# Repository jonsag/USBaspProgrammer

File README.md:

# USBaspProgrammer

My adaption of [Thomas Fischl's construction](https://www.fischl.de/usbasp/).  

This README concentrates on using ATmega88, and uploading it with avrisp, with a device such as [this one](https://github.com/jonsag/ardAVRProgrammer).  
Use the ICSP header on the programmer, and remember to set jumper J2.  

## Compile and upload

Put the ATmega88 in the programming device, and  

>$ cd Firmware/firmware

Test avrdude  

>$ make avrdude

    avrdude -c avrisp -p atmega88 -P /dev/ttyUSB0 -b 19200 -v

    avrdude: Version 6.3
            Copyright (c) 2000-2005 Brian Dean, http://www.bdmicro.com/
            Copyright (c) 2007-2014 Joerg Wunsch

            System wide configuration file is "/etc/avrdude.conf"
            User configuration file is "/home/jon/.avrduderc"
            User configuration file does not exist or is not a regular file, skipping

            Using Port                    : /dev/ttyUSB0
            Using Programmer              : avrisp
            Overriding Baud Rate          : 19200
            AVR Part                      : ATmega88
            Chip Erase delay              : 9000 us
            PAGEL                         : PD7
            BS2                           : PC2
            RESET disposition             : dedicated
            RETRY pulse                   : SCK
            serial program mode           : yes
            parallel program mode         : yes
            Timeout                       : 200
            StabDelay                     : 100
            CmdexeDelay                   : 25
            SyncLoops                     : 32
            ByteDelay                     : 0
            PollIndex                     : 3
            PollValue                     : 0x53
            Memory Detail                 :

                                    Block Poll               Page                       Polled
            Memory Type Mode Delay Size  Indx Paged  Size   Size #Pages MinW  MaxW   ReadBack
            ----------- ---- ----- ----- ---- ------ ------ ---- ------ ----- ----- ---------
            eeprom        65    20     4    0 no        512    4      0  3600  3600 0xff 0xff
            flash         65     6    64    0 yes      8192   64    128  4500  4500 0xff 0xff
            lfuse          0     0     0    0 no          1    0      0  4500  4500 0x00 0x00
            hfuse          0     0     0    0 no          1    0      0  4500  4500 0x00 0x00
            efuse          0     0     0    0 no          1    0      0  4500  4500 0x00 0x00
            lock           0     0     0    0 no          1    0      0  4500  4500 0x00 0x00
            calibration    0     0     0    0 no          1    0      0     0     0 0x00 0x00
            signature      0     0     0    0 no          3    0      0     0     0 0x00 0x00

            Programmer Type : STK500
            Description     : Atmel AVR ISP
            Hardware Version: 2
            Firmware Version: 1.18
            Topcard         : Unknown
            Vtarget         : 0.0 V
            Varef           : 0.0 V
            Oscillator      : Off
            SCK period      : 0.1 us

    avrdude: AVR device initialized and ready to accept instructions

    Reading | ################################################## | 100% 0.08s

    avrdude: Device signature = 0x1e930a (probably m88)
    avrdude: safemode: hfuse reads as DF
    avrdude: safemode: efuse reads as F9

    avrdude: safemode: hfuse reads as DF
    avrdude: safemode: efuse reads as F9
    avrdude: safemode: Fuses OK (E:F9, H:DF, L:62)

    avrdude done.  Thank you.

Clean, compile, upload and set fuses  

>$ make clean

    rm -f main.hex main.lst main.obj main.cof main.list main.map main.eep.hex main.bin *.o main.s usbdrv/*.o

>$ make main.hex

    avr-gcc -Wall -O2 -Iusbdrv -I. -mmcu=atmega88  -c usbdrv/usbdrv.c -o usbdrv/usbdrv.o
    avr-gcc -Wall -O2 -Iusbdrv -I. -mmcu=atmega88  -x assembler-with-cpp -c usbdrv/usbdrvasm.S -o usbdrv/usbdrvasm.o
    avr-gcc -Wall -O2 -Iusbdrv -I. -mmcu=atmega88  -c usbdrv/oddebug.c -o usbdrv/oddebug.o
    avr-gcc -Wall -O2 -Iusbdrv -I. -mmcu=atmega88  -c isp.c -o isp.o
    avr-gcc -Wall -O2 -Iusbdrv -I. -mmcu=atmega88  -c clock.c -o clock.o
    avr-gcc -Wall -O2 -Iusbdrv -I. -mmcu=atmega88  -x assembler-with-cpp -c tpi.S -o tpi.o
    avr-gcc -Wall -O2 -Iusbdrv -I. -mmcu=atmega88  -c main.c -o main.o
    avr-gcc -Wall -O2 -Iusbdrv -I. -mmcu=atmega88  -o main.bin usbdrv/usbdrv.o usbdrv/usbdrvasm.o usbdrv/oddebug.o isp.o clock.o tpi.o main.o -Wl,-Map,main.map
    rm -f main.hex main.eep.hex
    avr-objcopy -j .text -j .data -O ihex main.bin main.hex

>$ make flash

    avrdude -c avrisp -p atmega88 -P /dev/ttyUSB0 -b 19200 -U flash:w:main.hex

    avrdude: AVR device initialized and ready to accept instructions

    Reading | ################################################## | 100% 0.08s

    avrdude: Device signature = 0x1e930a (probably m88)
    avrdude: NOTE: "flash" memory has been specified, an erase cycle will be performed
            To disable this feature, specify the -D option.
    avrdude: erasing chip
    avrdude: reading input file "main.hex"
    avrdude: input file main.hex auto detected as Intel Hex
    avrdude: writing flash (4400 bytes):

    Writing | ################################################## | 100% 7.60s

    avrdude: 4400 bytes of flash written
    avrdude: verifying flash memory against main.hex:
    avrdude: load data flash data from input file main.hex:
    avrdude: input file main.hex auto detected as Intel Hex
    avrdude: input file main.hex contains 4400 bytes
    avrdude: reading on-chip flash data:

    Reading | ################################################## | 100% 5.38s

    avrdude: verifying ...
    avrdude: 4400 bytes of flash verified

    avrdude: safemode: Fuses OK (E:F9, H:DF, L:62)

    avrdude done.  Thank you.

>$ make fuses

    avrdude -c avrisp -p atmega88 -P /dev/ttyUSB0 -b 19200 -u -U hfuse:w:0xDD:m -U lfuse:w:0xFF:m

    avrdude: AVR device initialized and ready to accept instructions

    Reading | ################################################## | 100% 0.08s

    avrdude: Device signature = 0x1e930a (probably m88)
    avrdude: reading input file "0xDD"
    avrdude: writing hfuse (1 bytes):

    Writing | ################################################## | 100% 0.09s

    avrdude: 1 bytes of hfuse written
    avrdude: verifying hfuse memory against 0xDD:
    avrdude: load data hfuse data from input file 0xDD:
    avrdude: input file 0xDD contains 1 bytes
    avrdude: reading on-chip hfuse data:

    Reading | ################################################## | 100% 0.03s

    avrdude: verifying ...
    avrdude: 1 bytes of hfuse verified
    avrdude: reading input file "0xFF"
    avrdude: writing lfuse (1 bytes):

    Writing | ################################################## | 100% 0.09s

    avrdude: 1 bytes of lfuse written
    avrdude: verifying lfuse memory against 0xFF:
    avrdude: load data lfuse data from input file 0xFF:
    avrdude: input file 0xFF contains 1 bytes
    avrdude: reading on-chip lfuse data:

    Reading | ################################################## | 100% 0.03s

    avrdude: verifying ...
    avrdude: 1 bytes of lfuse verified

    avrdude done.  Thank you.

## Define device rules

>$ sudo cp \<PATH>/Documents/linux-nonroot/99-USBasp.rules /etc/udev/rules.d/99-USBasp.rules
>
>$ sudo udevadm control --reload-rules

## From Thomas Fischl's README

### USE PRECOMPILED VERSION  

Firmware:  
Flash "Firmware/precompiled/usbasp.atmega88.xxxx-xx-xx.hex" or "Firmware/precompiled/usbaspatmega8.xxxx-xx-xx.hex" to the used controller with a working programmer (e.g. with avrdude, uisp, ...). Set jumper J2 to activate USBasp firmware update function.  
You have to change the fuse bits for external crystal (see "make fuses").  
\# TARGET=atmega8    HFUSE=0xc9  LFUSE=0xef  
\# TARGET=atmega48   HFUSE=0xdd  LFUSE=0xff  
\# TARGET=atmega88   HFUSE=0xdd  LFUSE=0xff  

### Setting jumpers

J1 Power target  
    Supply target with 5V (USB voltage). Be careful with this option, the circuit isn't protected against short circuit!  
J2 Jumper for firmware upgrade (not self-upgradable)  
    Set this jumper for flashing the ATMega(4)8 of USBasp with another working programmer.  
J3 SCK option  
    If the target clock is lower than 1,5 MHz, you have to set this jumper. Then SCK is scaled down from 375 kHz to about 8 kHz  

### BUILDING AND INSTALLING FROM SOURCE CODE

#### Firmware

To compile the firmware  

1. install the GNU toolchain for AVR microcontrollers (avr-gcc, avr-libc),  
2. change directory to Firmware/firmware/  
3. run "make main.hex"  
4. flash "main.hex" to the ATMega(4)8. E.g. with uisp or avrdude (check the Makefile option "make flash"). To flash the firmware you have to set jumper J2 and connect USBasp to a working programmer.  
 You have to change the fuse bits for external crystal, (check the Makefile option "make fuses").  

#### Software (avrdude)

AVRDUDE supports USBasp since version 5.2.  

1. install libusb: [http://libusb.sourceforge.net/](http://libusb.sourceforge.net/)  
2. get latest avrdude release: [http://download.savannah.gnu.org/releases/avrdude/](http://download.savannah.gnu.org/releases/avrdude/)  
3. cd avrdude-X.X.X  
4. configure to your environment:  
./bootstrap (I had to comment out the two if-blocks which verify the installed versions of autoconf and automake)  
./configure  
5. compile and install it:  
make  
make install  

### Notes

To use USBasp as non-root, you have to define some device rules. See Documents/linux-nonroot for an example.  

### MORE INFORMATION

For more information on USBasp and it's components please visit the following URLs:  

USBasp .......................... [http://www.fischl.de/usbasp/](http://www.fischl.de/usbasp/)  
  
Firmware-only V-USB driver ...... [http://www.obdev.at/products/vusb/](http://www.obdev.at/products/vusb/)  
avrdude ......................... [http://www.nongnu.org/avrdude/](http://www.nongnu.org/avrdude/)  
libusb .......................... [http://libusb.sourceforge.net/](http://libusb.sourceforge.net/)  
libusb-win32 .................... [http://libusb-win32.sourceforge.net/](http://libusb-win32.sourceforge.net/)  

## Troubleshooting

### Compiling problem

    usbdrv/usbdrv.h:455:6: error: variable ‘usbDescriptorDevice’ must be const in order to be put into read-only section by means of ‘__attribute__((progmem))’
 char usbDescriptorDevice[];

Solution at [https://openrcforums.com/forum/viewtopic.php?t=2731](https://openrcforums.com/forum/viewtopic.php?t=2731), from Mon Feb 04, 2013  

    This issue is resolved I just wanted to document it here.

    Usbasp uses V-usb for usb communications. Usbasp includes V-usb in it's source code. The version of V-usb included in Usbasp is not the latest and would not compile with a recent avr-gcc. This issue affected er9x over a year ago.

    When trying to compile the 2009 or 2011 versions of Usbasp from http://www.fischl.de/usbasp/ I got about a dozen of these errors.
    CODE: SELECT ALL

    usbdrv/usbdrv.h:451:6: error: variable ‘usbDescriptorDevice’ must be const in order to be put into read-only section by means of ‘__attribute__((progmem))’
    The solution was to remove the ./firmware/usbdrv directory from the Usbasp source and replace it with the source from http://www.obdev.at/downloads/vusb/vusb-20121206.tar.gz . Then I was able to compile Usbasp. I tested both the 2009 and 2011 versions on a programmer and was able to program a MCU.

    Not sure when avr-gcc became picky about this issue or if that is even the issue. Nor do I know why my Ubuntuish 'Linux Mint 14 Nadia' calls the package gcc-avr. Anyway this is what versions of the relevant ( I think) packages I have installed.

    ii avr-libc 1:1.8.0-2 all Standard C library for Atmel AVR developm
    ii binutils-avr 2.20.1-3 amd64 Binary utilities supporting Atmel's AVR t
    ii gcc-avr 1:4.7.0-2 amd64 The GNU C compiler (cross compiler for av

## My notes

Connections on different MCUs  

            10Pin           6pin    ATmega8/88/328/328P     ATtiny4313      ATtiny85  
MOSI    ->  1           ->  4   ->  17/PB3                  17/PB5          5/AREF/PB0  
MISO    ->  9           ->  1   ->  18/PB4                  18/PB6          6/PB1  
SCK     ->  7           ->  3   ->  19/PB5                  19/PB7          7/PB2  
RST     ->  5           ->  5   ->  1/RESET/PC6,21/AREF     1/RESET/PA2     1/RESET/PB5  
VCC     ->  2           ->  2   ->  7/VCC                   20/VCC          8/VCC  
GND     ->  4,6,8,10    ->  6   ->  8/GND                   10/GND          4/GND  
XTAL1                               9/XTAL1                 5/XTAL1         2/XTAL1
XTAL2                               10/XTAL2                4/XTAL2         3/XTAL2

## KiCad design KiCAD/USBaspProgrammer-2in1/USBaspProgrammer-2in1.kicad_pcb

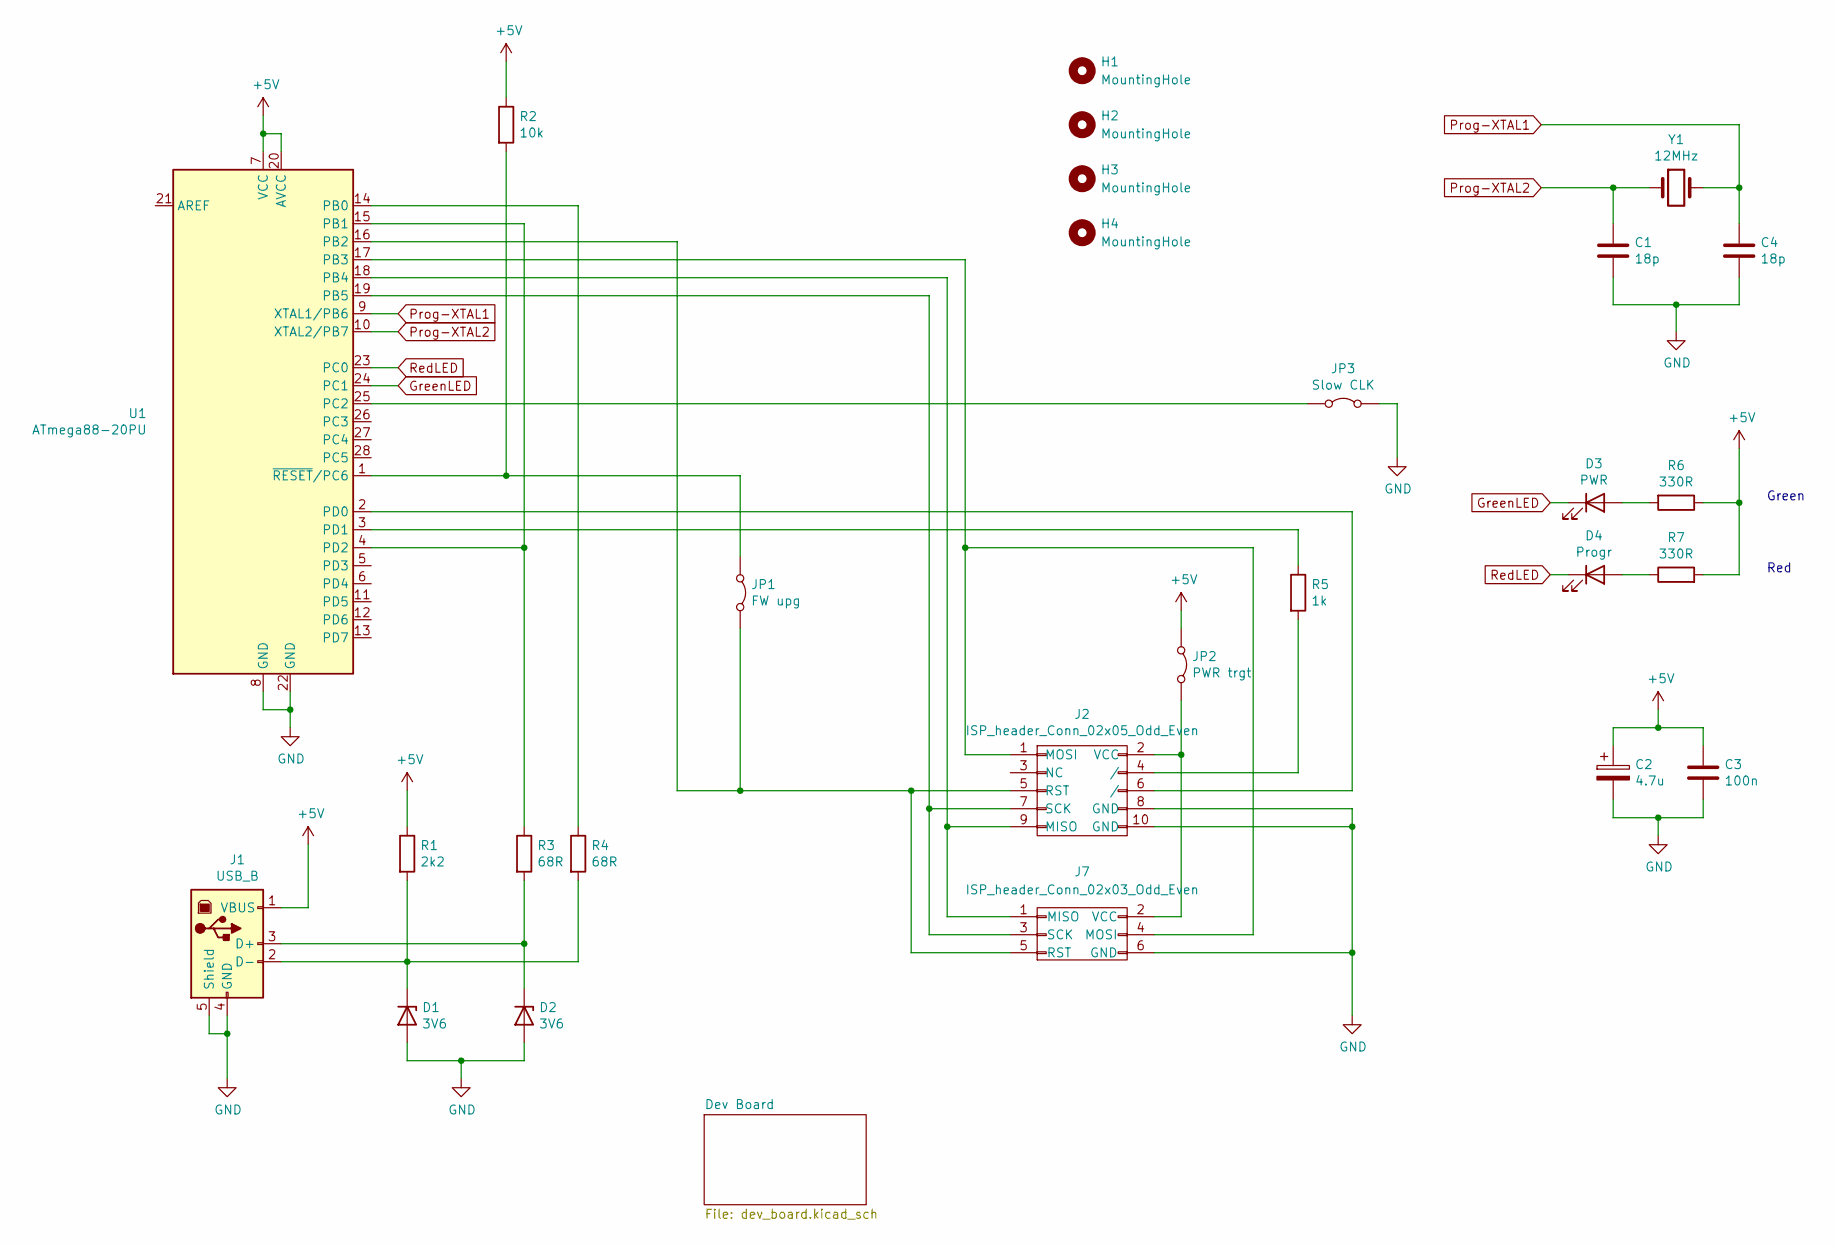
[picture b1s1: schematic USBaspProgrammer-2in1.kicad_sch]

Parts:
C1, C4: 18p; C_Disc_D3.0mm_W1.6mm_P2.50mm_larg
C2: 4.7u; CP_Radial_D5.0mm_P2.00mm_larger
C3: 100n; C_Disc_D7.5mm_W2.5mm_P5.00mm_larger
D1, D2: 3V6; D_DO-35_SOD27_P7.62mm_Horizontal_large
D3: PWR; LED_D5.0mm_larger_pads
D4: Progr; LED_D5.0mm_larger_pads
H1, H2, H3, H4: MountingHole; MountingHole_3.2mm_M3
J1: USB_B; USB_B_OST_USB-B1HSxx_Horizontal_large
J2: ISP_header_Conn_02x05_Odd_Even; IDC-Header_2x05_P2.54mm_Vertical_large
J7: ISP_header_Conn_02x03_Odd_Even; IDC-Header_2x03_P2.54mm_Horizontal_large
JP1: FW upg; Jumper_1x02_P2.54mm_large
JP2: PWR trgt; Jumper_1x02_P2.54mm_large
JP3: Slow CLK; Jumper_1x02_P2.54mm_large
R1: 2k2; R_Axial_DIN0207_L6.3mm_D2.5mm_P10.16mm_Horizontal_large
R2: 10k; R_Axial_DIN0207_L6.3mm_D2.5mm_P10.16mm_Horizontal_large
R3, R4: 68R; R_Axial_DIN0207_L6.3mm_D2.5mm_P10.16mm_Horizontal_large
R5: 1k; R_Axial_DIN0207_L6.3mm_D2.5mm_P10.16mm_Horizontal_large
R6, R7: 330R; R_Axial_DIN0207_L6.3mm_D2.5mm_P10.16mm_Horizontal_large
U1: ATmega88-20PU; DIP-28_W7.62mm_LongPads w socket
Y1: 12MHz; Crystal_HC49-4H_Vertical_large

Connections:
+5V: C2.1, C3.1, J1.1 (VBUS), JP2.1 (A), R1.1, R2.1, R6.1, R7.2, U1.7 (VCC), U1.20 (AVCC)
GND: C1.2, C2.2, C3.2, C4.2, D1.2 (A), D2.2 (A), J1.4 (GND), J1.5 (Shield), J2.8 (GND), J2.10 (GND), J7.6 (GND), JP3.2 (B), U1.8 (GND), U1.22 (GND); also elsewhere on the board
GreenLED: D3.1 (K), U1.24 (PC1)
unnamed: D1.1 (K), J1.2 (D-), R1.2, R4.2
unnamed: D2.1 (K), J1.3 (D+), R3.2
unnamed: D3.2 (A), R6.2
unnamed: D4.2 (A), R7.1
unnamed: J2.9 (MISO), J7.1 (MISO), U1.18 (PB4)
unnamed: J2.1 (MOSI), J7.4 (MOSI), U1.17 (PB3)
unnamed: J2.5 (RST), J7.5 (RST), JP1.2 (B), U1.16 (PB2)
unnamed: J2.7 (SCK), J7.3 (SCK), U1.19 (PB5)
unnamed: J2.2 (VCC), J7.2 (VCC), JP2.2 (B)
unnamed: J2.4 (/), R5.2
unnamed: JP1.1 (A), R2.2, U1.1 (~RESET/PC6)
unnamed: JP3.1 (A), U1.25 (PC2)
unnamed: R4.1, U1.14 (PB0)
unnamed: R3.1, U1.4 (PD2), U1.15 (PB1)
unnamed: J2.6 (/), U1.2 (PD0)
unnamed: R5.1, U1.3 (PD1)
Prog-XTAL1: C4.1, U1.9 (XTAL1/PB6), Y1.2
Prog-XTAL2: C1.1, U1.10 (XTAL2/PB7), Y1.1
RedLED: D4.1 (K), U1.23 (PC0)

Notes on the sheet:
Green
Red

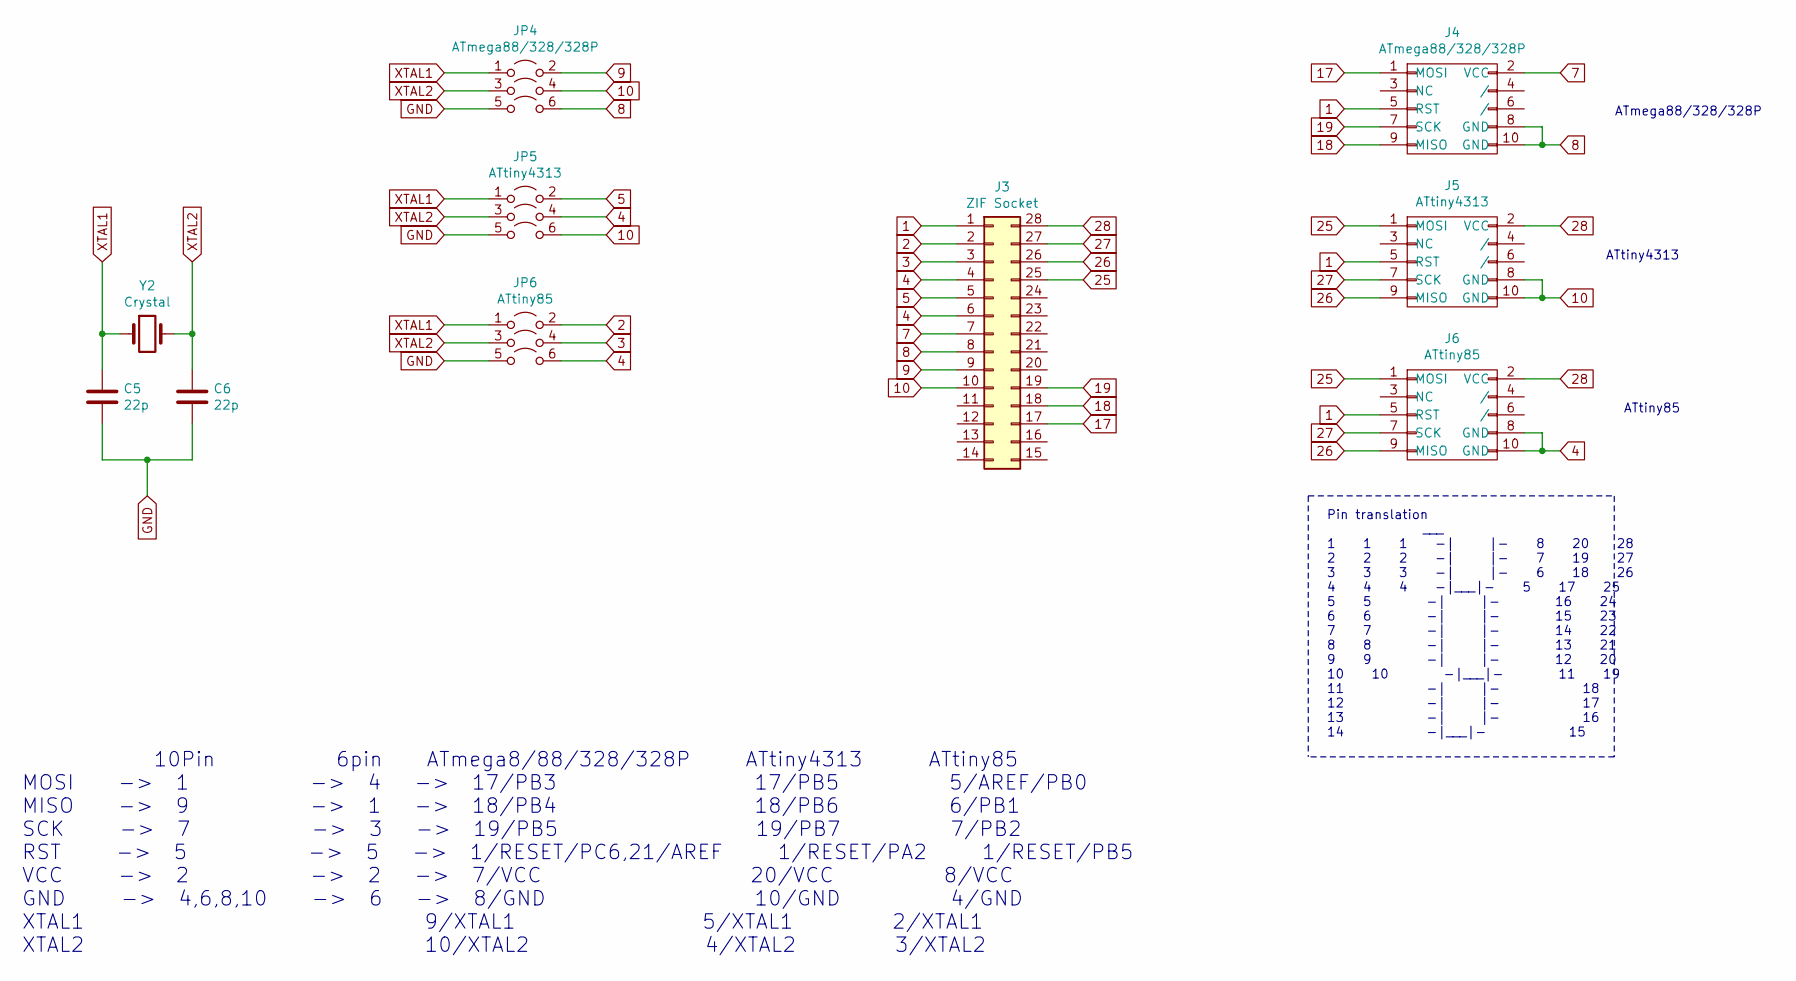
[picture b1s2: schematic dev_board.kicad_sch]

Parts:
C5, C6: 22p; C_Disc_D3.0mm_W1.6mm_P2.50mm_larg
J3: ZIF Socket; ZIF_DIP_Socket-28_W6.9_W7.62_W7.62_W12.7_W13.5_large
J4: ATmega88/328/328P; IDC-Header_2x05_P2.54mm_Vertical_large
J5: ATtiny4313; IDC-Header_2x05_P2.54mm_Vertical_large
J6: ATtiny85; IDC-Header_2x05_P2.54mm_Vertical_large
JP4: ATmega88/328/328P; 3-pole_jumper_2x03_P2.54mm_Vertical
JP5: ATtiny4313; 3-pole_jumper_2x03_P2.54mm_Vertical
JP6: ATtiny85; 3-pole_jumper_2x03_P2.54mm_Vertical
Y2: Crystal; Crystal_HC49-4H_Vertical_large

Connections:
1: J3.1, J4.5 (RST), J5.5 (RST), J6.5 (RST)
2: J3.2, JP6.2 (B)
3: J3.3, JP6.4
4: J3.4, J3.6, J6.8 (GND), J6.10 (GND), JP5.4, JP6.6
5: J3.5, JP5.2 (B)
7: J3.7, J4.2 (VCC)
8: J3.8, J4.8 (GND), J4.10 (GND), JP4.6
9: J3.9, JP4.2 (B)
10: J3.10, J5.8 (GND), J5.10 (GND), JP4.4, JP5.6
17: J3.17, J4.1 (MOSI)
18: J3.18, J4.9 (MISO)
19: J3.19, J4.7 (SCK)
25: J3.25, J5.1 (MOSI), J6.1 (MOSI)
26: J3.26, J5.9 (MISO), J6.9 (MISO)
27: J3.27, J5.7 (SCK), J6.7 (SCK)
28: J3.28, J5.2 (VCC), J6.2 (VCC)
GND: C5.2, C6.2, JP4.5, JP5.5, JP6.5; also elsewhere on the board
XTAL1: C5.1, JP4.1 (A), JP5.1 (A), JP6.1 (A), Y2.1
XTAL2: C6.1, JP4.3, JP5.3, JP6.3, Y2.2

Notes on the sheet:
ATtiny85
Pin translation ___ 1 1 1 -| |- 8 20 28 2 2 2 -| |- 7 19 27 3 3 3 -| |- 6 18 26 4 4 4 -|___|- 5 17 25 5 5 -| |- 16 24 6 6 -| |- 15 23 7 7 -| |- 14 22 8 8 -| |- 13 21 9 9 -| |- 12 20 10 10 -|___|- 11 19 11 -| |- 18 12 -| |- 17 13 -| |- 16 14 -|___|- 15
ATmega88/328/328P
10Pin 6pin ATmega8/88/328/328P ATtiny4313 ATtiny85 MOSI -> 1 -> 4 -> 17/PB3 17/PB5 5/AREF/PB0 MISO -> 9 -> 1 -> 18/PB4 18/PB6 6/PB1 SCK -> 7 -> 3 -> 19/PB5 19/PB7 7/PB2 RST -> 5 -> 5 -> 1/RESET/PC6,21/AREF 1/RESET/PA2 1/RESET/PB5 VCC -> 2 -> 2 -> 7/VCC 20/VCC 8/VCC GND -> 4,6,8,10 -> 6 -> 8/GND 10/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
ATtiny4313

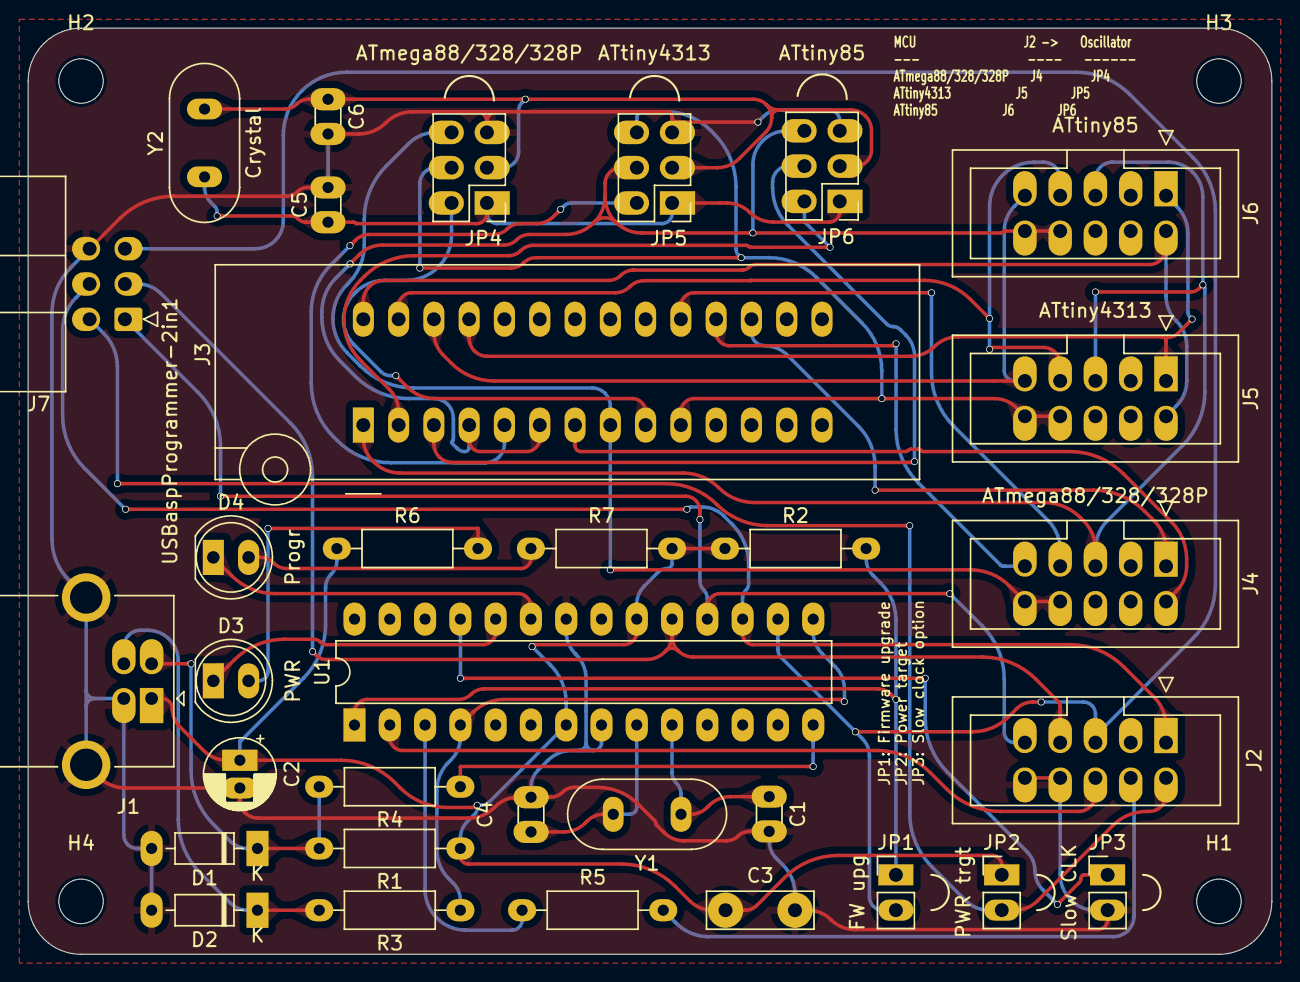
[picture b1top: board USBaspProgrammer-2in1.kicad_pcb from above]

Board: 2 copper layers, 89.5 x 66.7 mm, 37 parts (0 on the bottom side), 40 nets.

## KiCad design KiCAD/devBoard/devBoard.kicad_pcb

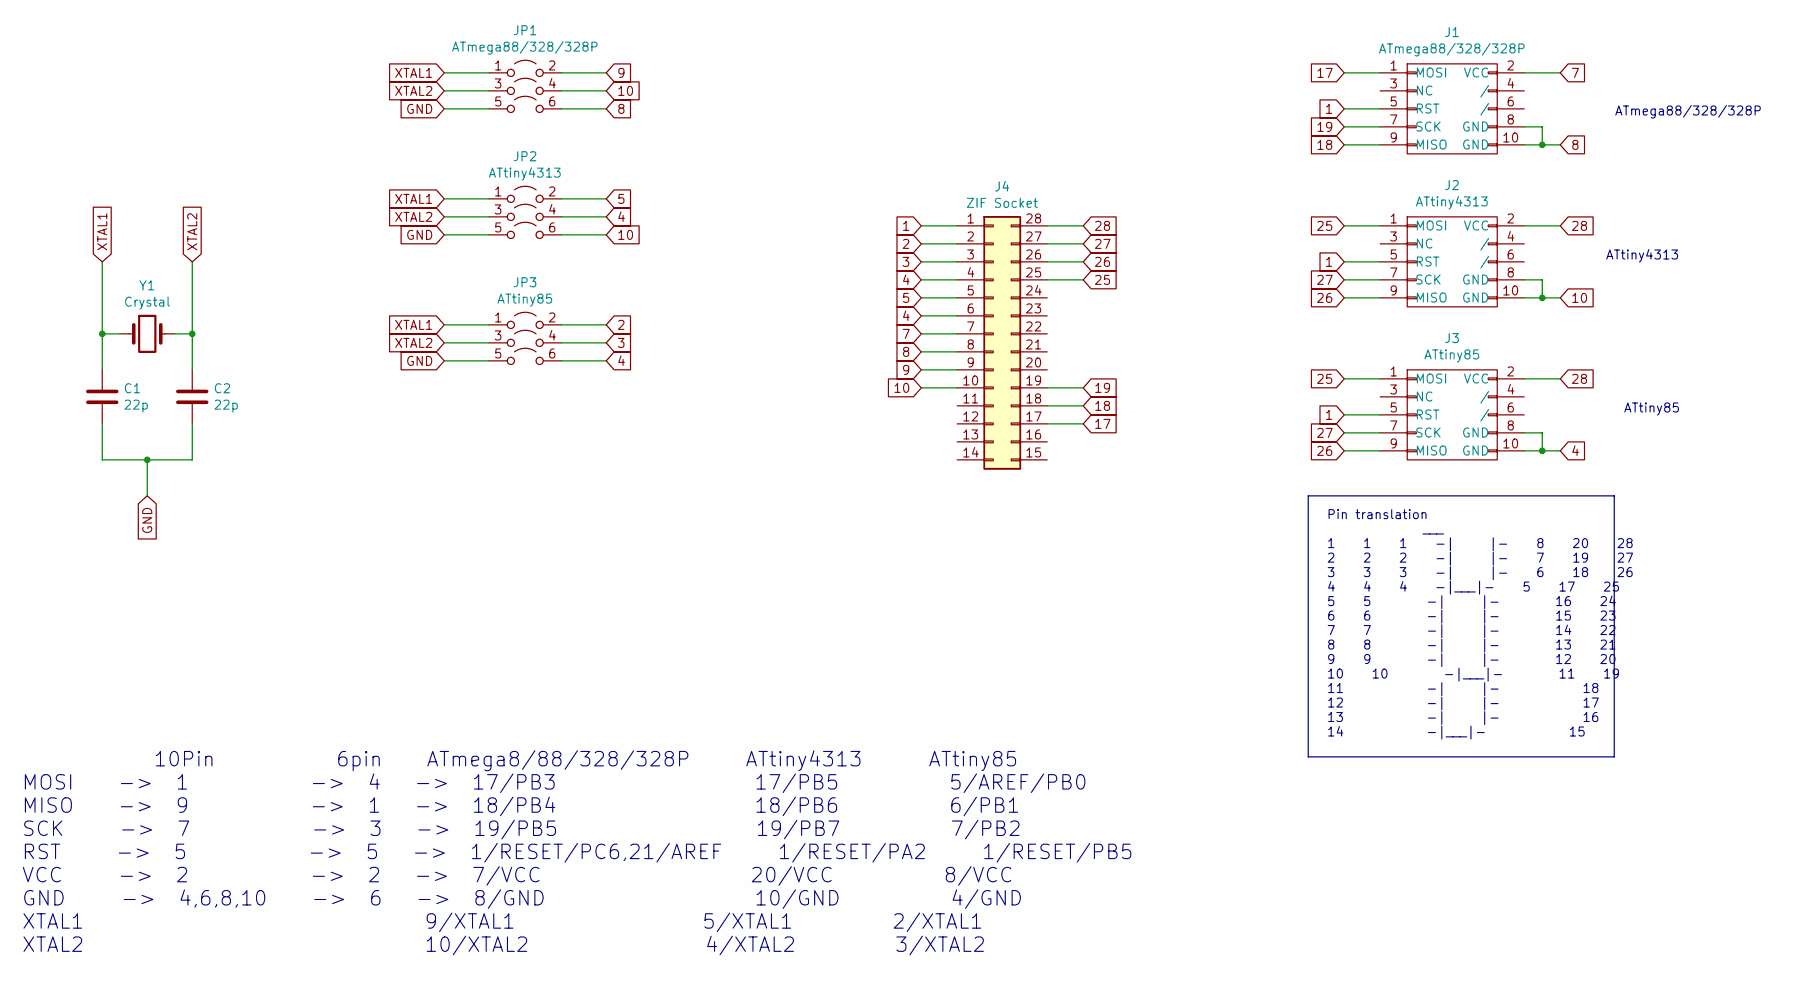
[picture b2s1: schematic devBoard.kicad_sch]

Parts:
C1, C2: 22p; C_Disc_D3.0mm_W1.6mm_P2.50mm_larg
J1: ATmega88/328/328P; IDC-Header_2x05_P2.54mm_Vertical_large
J2: ATtiny4313; IDC-Header_2x05_P2.54mm_Vertical_large
J3: ATtiny85; IDC-Header_2x05_P2.54mm_Vertical_large
J4: ZIF Socket; ZIF_DIP_Socket-28_W6.9_W7.62_W7.62_W12.7_W13.5_large
JP1: ATmega88/328/328P; 3-pole_jumper_2x03_P2.54mm_Vertical
JP2: ATtiny4313; 3-pole_jumper_2x03_P2.54mm_Vertical
JP3: ATtiny85; 3-pole_jumper_2x03_P2.54mm_Vertical
Y1: Crystal; 2-pin_Crystal_header_large

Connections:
1: J1.5 (RST), J2.5 (RST), J3.5 (RST), J4.1
2: J4.2, JP3.2 (B)
3: J4.3, JP3.4
4: J3.8 (GND), J3.10 (GND), J4.4, J4.6, JP2.4, JP3.6
5: J4.5, JP2.2 (B)
7: J1.2 (VCC), J4.7
8: J1.8 (GND), J1.10 (GND), J4.8, JP1.6
9: J4.9, JP1.2 (B)
10: J2.8 (GND), J2.10 (GND), J4.10, JP1.4, JP2.6
17: J1.1 (MOSI), J4.17
18: J1.9 (MISO), J4.18
19: J1.7 (SCK), J4.19
25: J2.1 (MOSI), J3.1 (MOSI), J4.25
26: J2.9 (MISO), J3.9 (MISO), J4.26
27: J2.7 (SCK), J3.7 (SCK), J4.27
28: J2.2 (VCC), J3.2 (VCC), J4.28
GND: C1.2, C2.2, JP1.5, JP2.5, JP3.5
XTAL1: C1.1, JP1.1 (A), JP2.1 (A), JP3.1 (A), Y1.1
XTAL2: C2.1, JP1.3, JP2.3, JP3.3, Y1.2

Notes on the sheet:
ATtiny4313
ATmega88/328/328P
ATtiny85
Pin translation ___ 1 1 1 -| |- 8 20 28 2 2 2 -| |- 7 19 27 3 3 3 -| |- 6 18 26 4 4 4 -|___|- 5 17 25 5 5 -| |- 16 24 6 6 -| |- 15 23 7 7 -| |- 14 22 8 8 -| |- 13 21 9 9 -| |- 12 20 10 10 -|___|- 11 19 11 -| |- 18 12 -| |- 17 13 -| |- 16 14 -|___|- 15
10Pin 6pin ATmega8/88/328/328P ATtiny4313 ATtiny85 MOSI -> 1 -> 4 -> 17/PB3 17/PB5 5/AREF/PB0 MISO -> 9 -> 1 -> 18/PB4 18/PB6 6/PB1 SCK -> 7 -> 3 -> 19/PB5 19/PB7 7/PB2 RST -> 5 -> 5 -> 1/RESET/PC6,21/AREF 1/RESET/PA2 1/RESET/PB5 VCC -> 2 -> 2 -> 7/VCC 20/VCC 8/VCC GND -> 4,6,8,10 -> 6 -> 8/GND 10/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

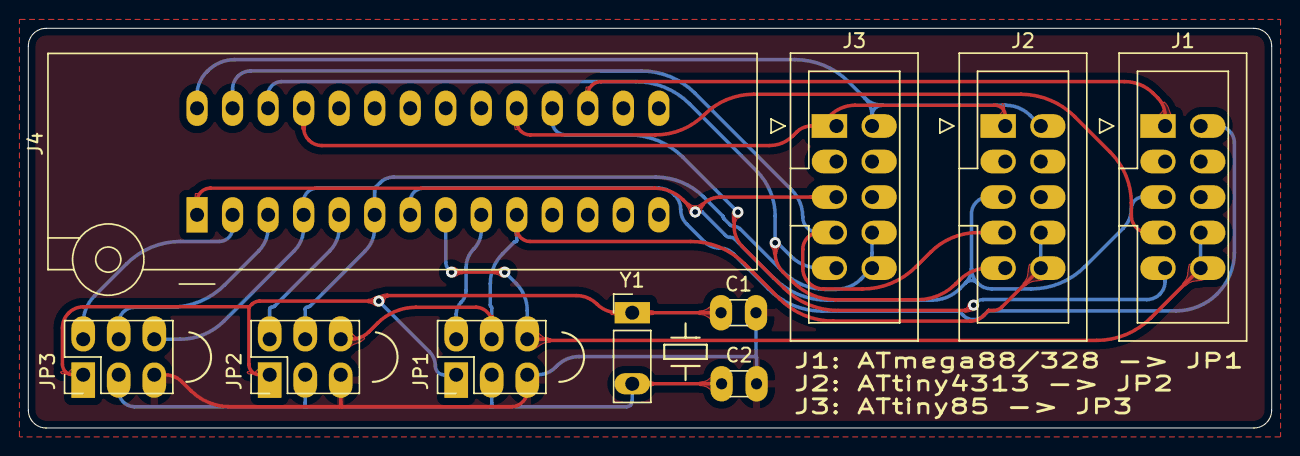
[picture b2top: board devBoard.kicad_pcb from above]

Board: 2 copper layers, 88.9 x 28.6 mm, 10 parts (0 on the bottom side), 19 nets.

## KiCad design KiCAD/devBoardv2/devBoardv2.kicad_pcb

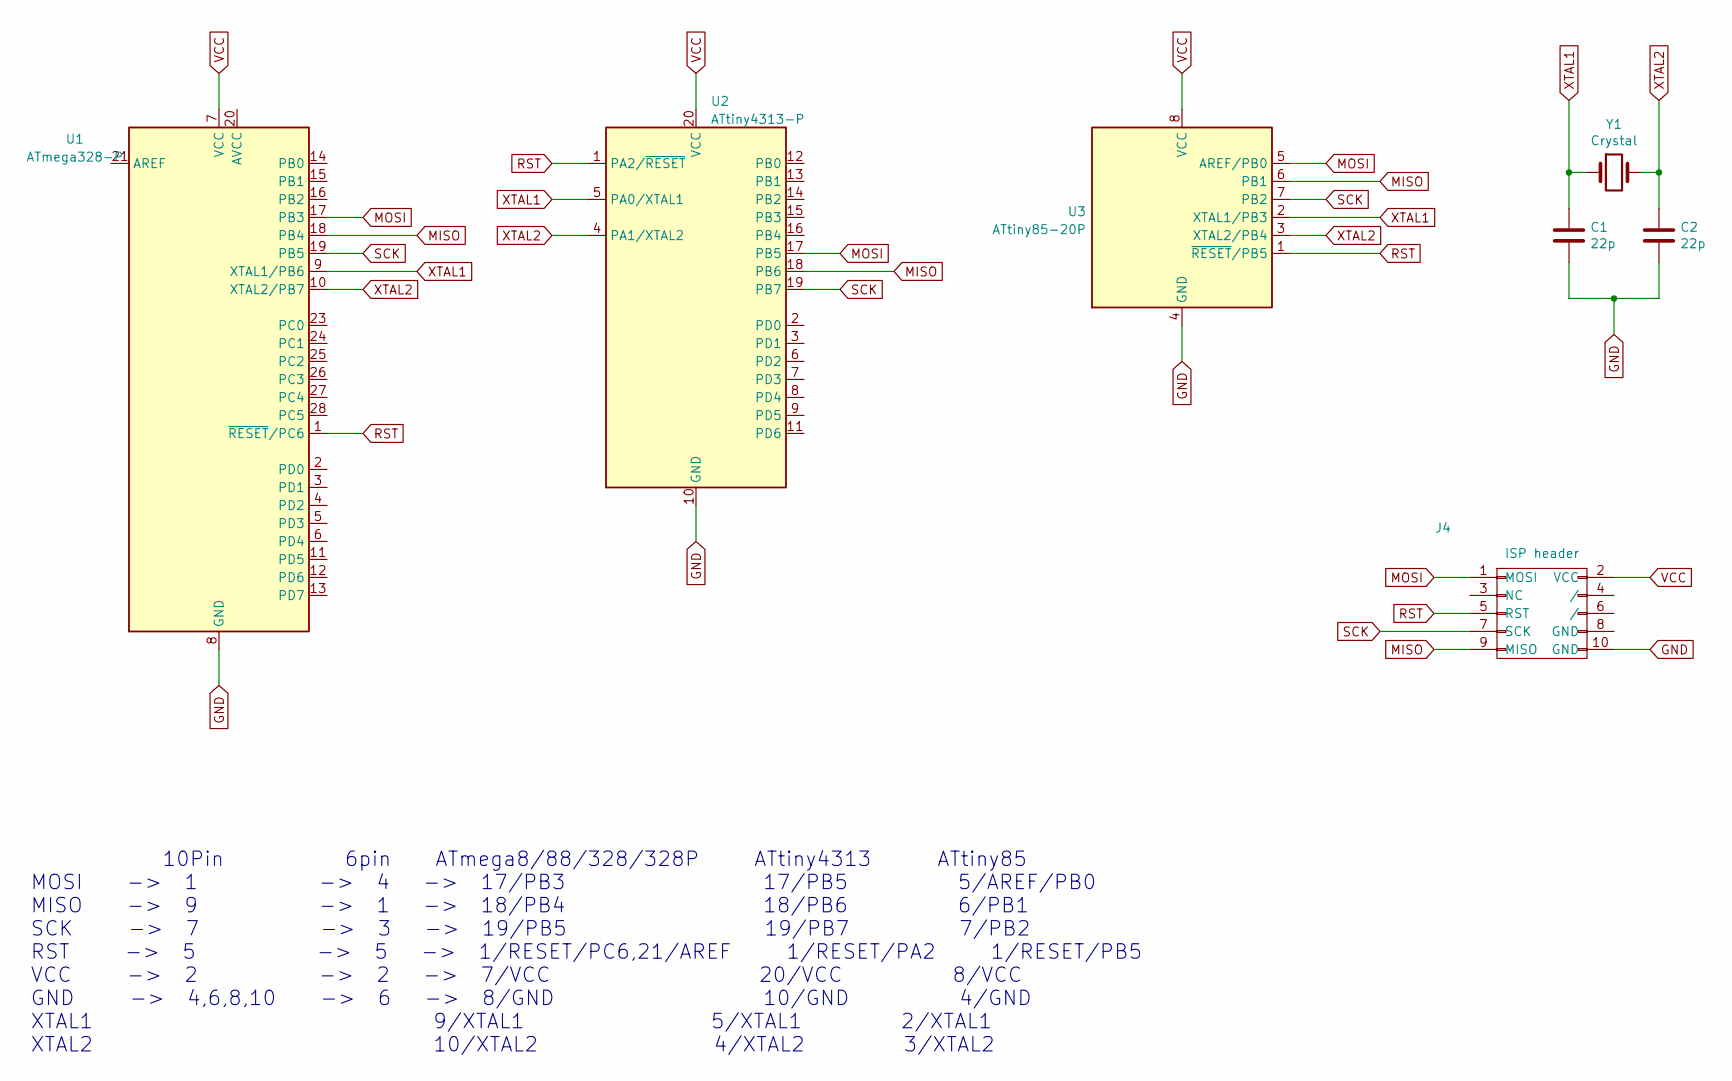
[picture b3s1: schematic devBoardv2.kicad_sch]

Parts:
C1, C2: 22p; C_Disc_D3.0mm_W1.6mm_P2.50mm_larg
J4: ISP header; IDC-Header_2x05_P2.54mm_Vertical_large
U1: ATmega328-P
U2: ATtiny4313-P
U3: ATtiny85-20P
Y1: Crystal; 2-pin_Crystal_header_large

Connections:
GND: C1.2, C2.2, J4.10 (GND), U1.8 (GND), U1.22 (GND), U2.10 (GND), U3.4 (GND)
MISO: J4.9 (MISO), U1.18 (PB4), U2.18 (PB6), U3.6 (PB1)
MOSI: J4.1 (MOSI), U1.17 (PB3), U2.17 (PB5), U3.5 (AREF/PB0)
RST: J4.5 (RST), U1.1 (~RESET/PC6), U2.1 (PA2/~RESET), U3.1 (~RESET/PB5)
SCK: J4.7 (SCK), U1.19 (PB5), U2.19 (PB7), U3.7 (PB2)
VCC: J4.2 (VCC), U1.7 (VCC), U2.20 (VCC), U3.8 (VCC)
XTAL1: C1.1, U1.9 (XTAL1/PB6), U2.5 (PA0/XTAL1), U3.2 (XTAL1/PB3), Y1.1
XTAL2: C2.1, U1.10 (XTAL2/PB7), U2.4 (PA1/XTAL2), U3.3 (XTAL2/PB4), Y1.2

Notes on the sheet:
10Pin 6pin ATmega8/88/328/328P ATtiny4313 ATtiny85 MOSI -> 1 -> 4 -> 17/PB3 17/PB5 5/AREF/PB0 MISO -> 9 -> 1 -> 18/PB4 18/PB6 6/PB1 SCK -> 7 -> 3 -> 19/PB5 19/PB7 7/PB2 RST -> 5 -> 5 -> 1/RESET/PC6,21/AREF 1/RESET/PA2 1/RESET/PB5 VCC -> 2 -> 2 -> 7/VCC 20/VCC 8/VCC GND -> 4,6,8,10 -> 6 -> 8/GND 10/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

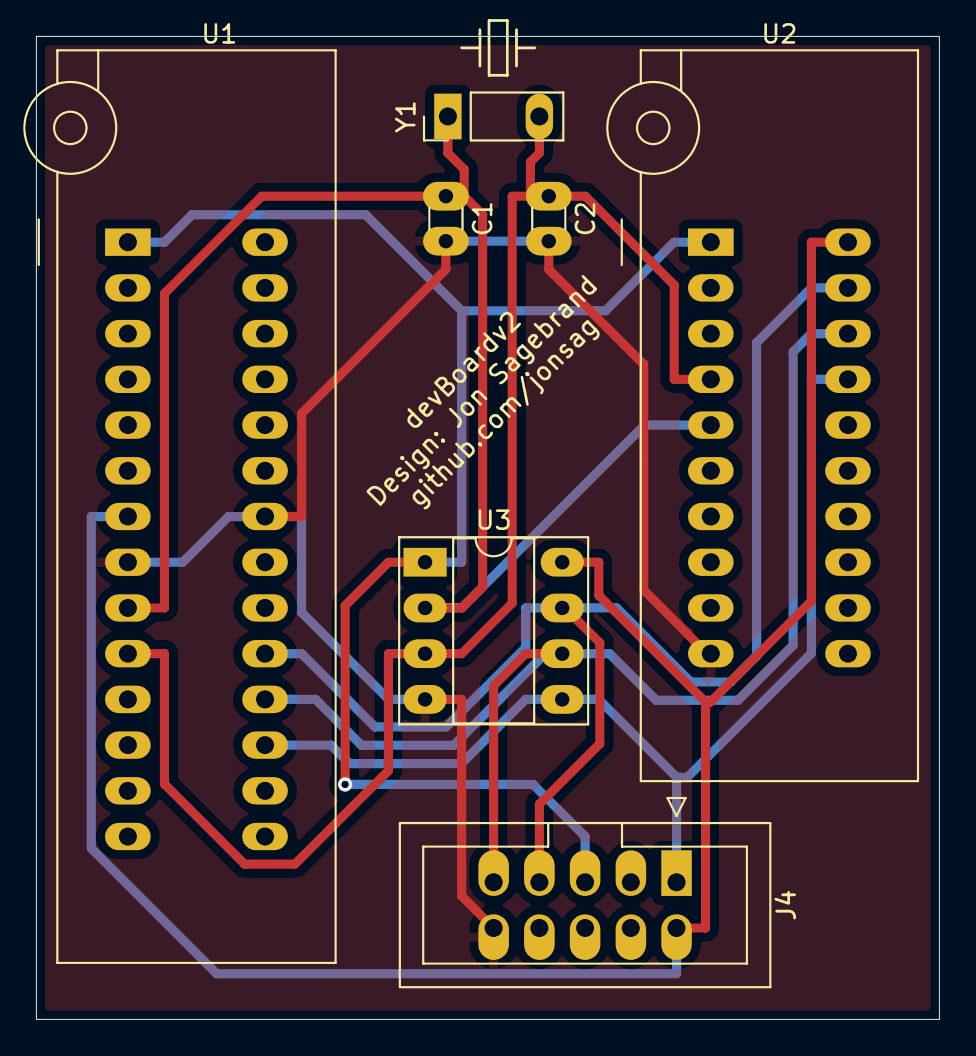
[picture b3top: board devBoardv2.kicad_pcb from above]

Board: 2 copper layers, 50.2 x 54.6 mm, 7 parts (0 on the bottom side), 8 nets.

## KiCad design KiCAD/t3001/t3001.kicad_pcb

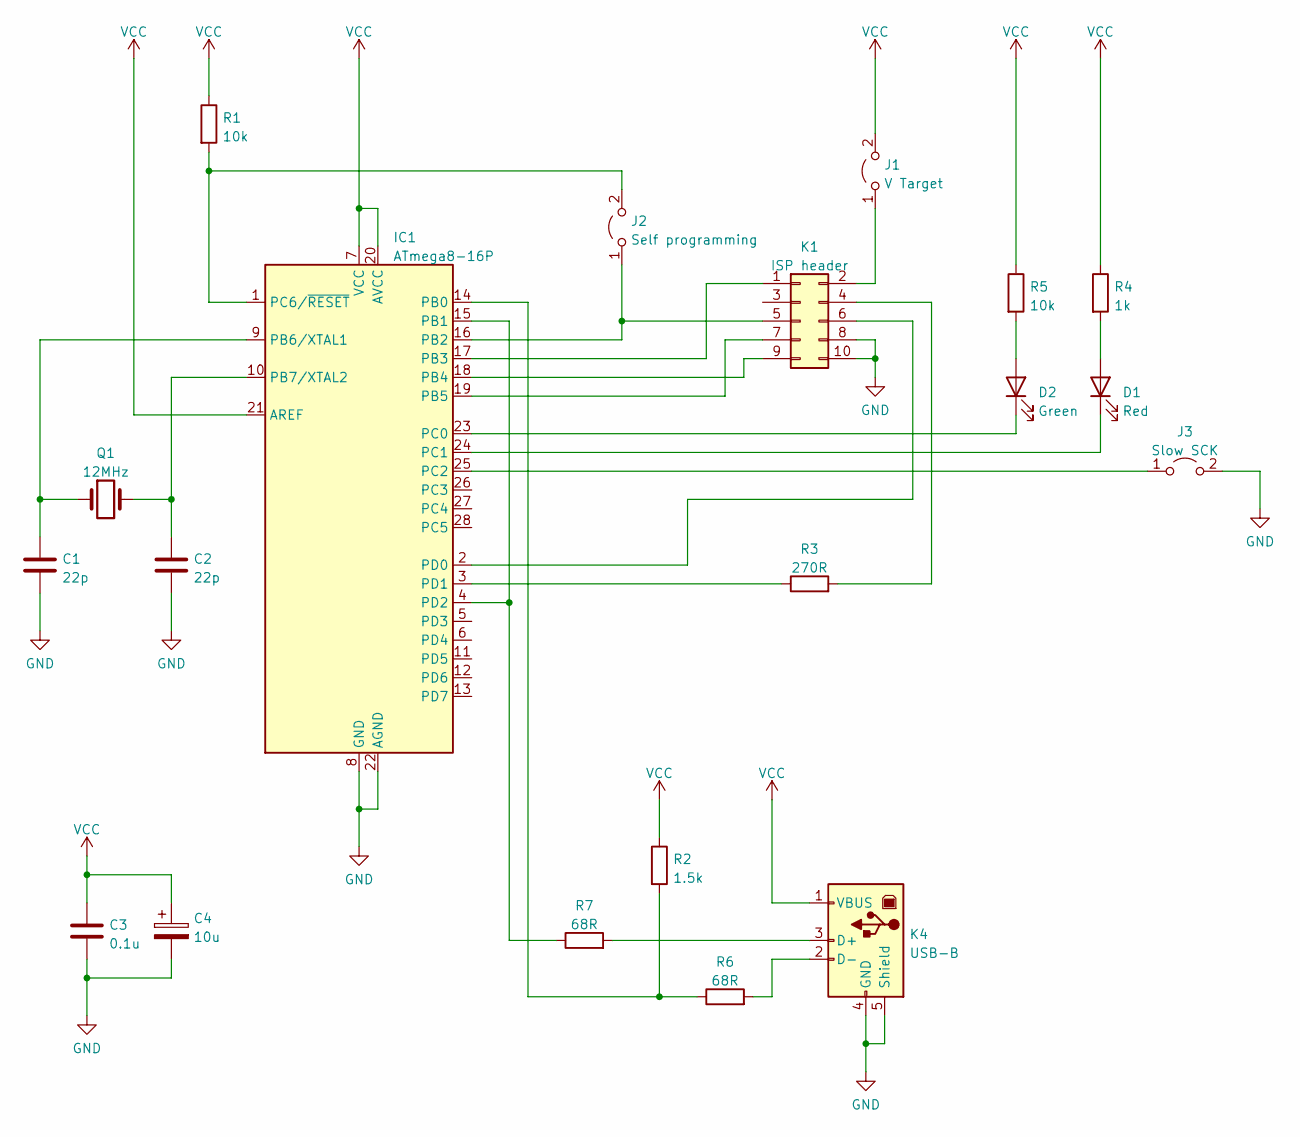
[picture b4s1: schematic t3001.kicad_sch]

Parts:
C1, C2: 22p; C_Disc_D3.0mm_W1.6mm_P2.50mm_larg
C3: 0.1u; C_Disc_D3.0mm_W1.6mm_P2.50mm_larg
C4: 10u; CP_Radial_D5.0mm_P2.50mm_larger_pads
D1: Red; LED_D5.0mm_larger_pads
D2: Green; LED_D5.0mm_larger_pads
IC1: ATmega8-16P; DIP-28_W7.62mm_LongPads
J1: V Target; Jumper_1x02_P2.54mm_large
J2: Self programming; Jumper_1x02_P2.54mm_large
J3: Slow SCK; Jumper_1x02_P2.54mm_large
K1: ISP header; 2x5_ISP_header_large
K4: USB-B; USB_B_OST_USB-B1HSxx_Horizontal_large
Q1: 12MHz; Crystal_HC49-4H_Vertical_large
R1, R5: 10k; R_Axial_DIN0207_L6.3mm_D2.5mm_P10.16mm_Horizontal_larger_pa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
R2: 1.5k; R_Axial_DIN0207_L6.3mm_D2.5mm_P10.16mm_Horizontal_larger_pa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
R3: 270R; R_Axial_DIN0207_L6.3mm_D2.5mm_P10.16mm_Horizontal_larger_pa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
R4: 1k; R_Axial_DIN0207_L6.3mm_D2.5mm_P10.16mm_Horizontal_larger_pa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
R6, R7: 68R; R_Axial_DIN0207_L6.3mm_D2.5mm_P10.16mm_Horizontal_larger_pa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

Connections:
GND: C1.2, C2.2, C3.2, C4.2, IC1.8 (GND), IC1.22 (AGND), J3.2 (B), K1.8, K1.10, K4.4 (GND), K4.5 (Shield)
unnamed: C1.1, IC1.9 (PB6/XTAL1), Q1.1
unnamed: C2.1, IC1.10 (PB7/XTAL2), Q1.2
unnamed: D1.1 (K), IC1.24 (PC1)
unnamed: D1.2 (A), R4.2
unnamed: D2.1 (K), IC1.23 (PC0)
unnamed: D2.2 (A), R5.2
unnamed: IC1.1 (PC6/~RESET), J2.2 (B), R1.2
unnamed: IC1.2 (PD0), K1.6
unnamed: IC1.3 (PD1), R3.1
unnamed: IC1.14 (PB0), R2.2, R6.1
unnamed: IC1.4 (PD2), IC1.15 (PB1), R7.1
unnamed: IC1.16 (PB2), J2.1 (A), K1.5
unnamed: IC1.17 (PB3), K1.1
unnamed: IC1.18 (PB4), K1.9
unnamed: IC1.19 (PB5), K1.7
unnamed: IC1.25 (PC2), J3.1 (A)
unnamed: J1.1 (A), K1.2
unnamed: K1.4, R3.2
unnamed: K4.2 (D-), R6.2
unnamed: K4.3 (D+), R7.2
VCC: C3.1, C4.1, IC1.7 (VCC), IC1.20 (AVCC), IC1.21 (AREF), J1.2 (B), K4.1 (VBUS), R1.1, R2.1, R4.1, R5.1

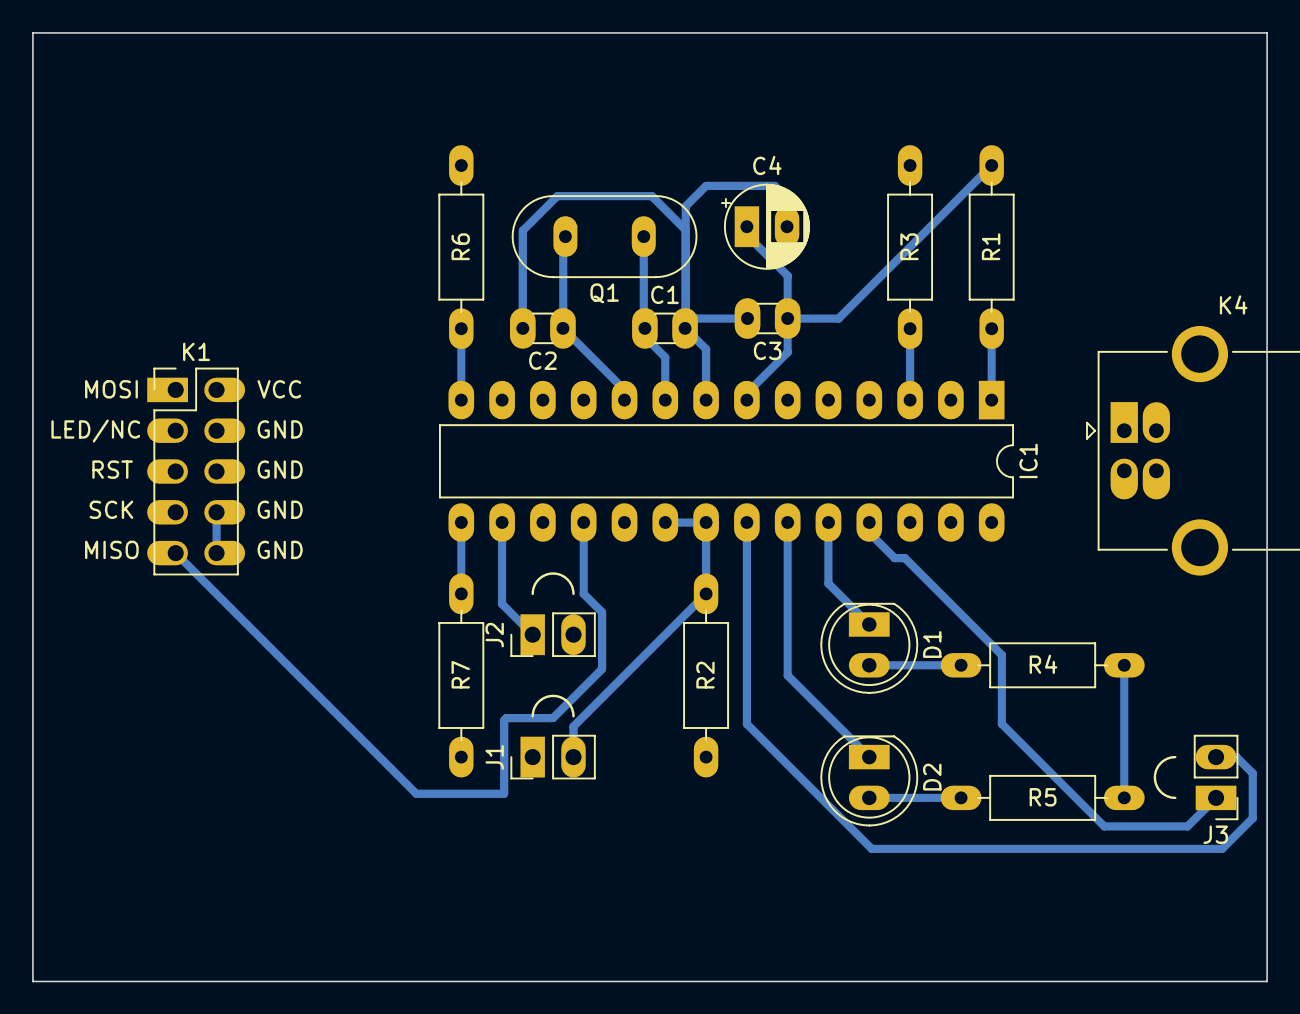
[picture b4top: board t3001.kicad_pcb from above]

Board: 2 copper layers, 76.8 x 59.1 mm, 20 parts (0 on the bottom side), 22 nets.
